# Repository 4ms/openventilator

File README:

This project is a collaboration to update the OpenVentilator files provided by Medtronic to modern KiCad format as well as update BoM to currently available components.

If you'd like to contribute, please contact Seth (seth@kipro-pcb.com) for details.

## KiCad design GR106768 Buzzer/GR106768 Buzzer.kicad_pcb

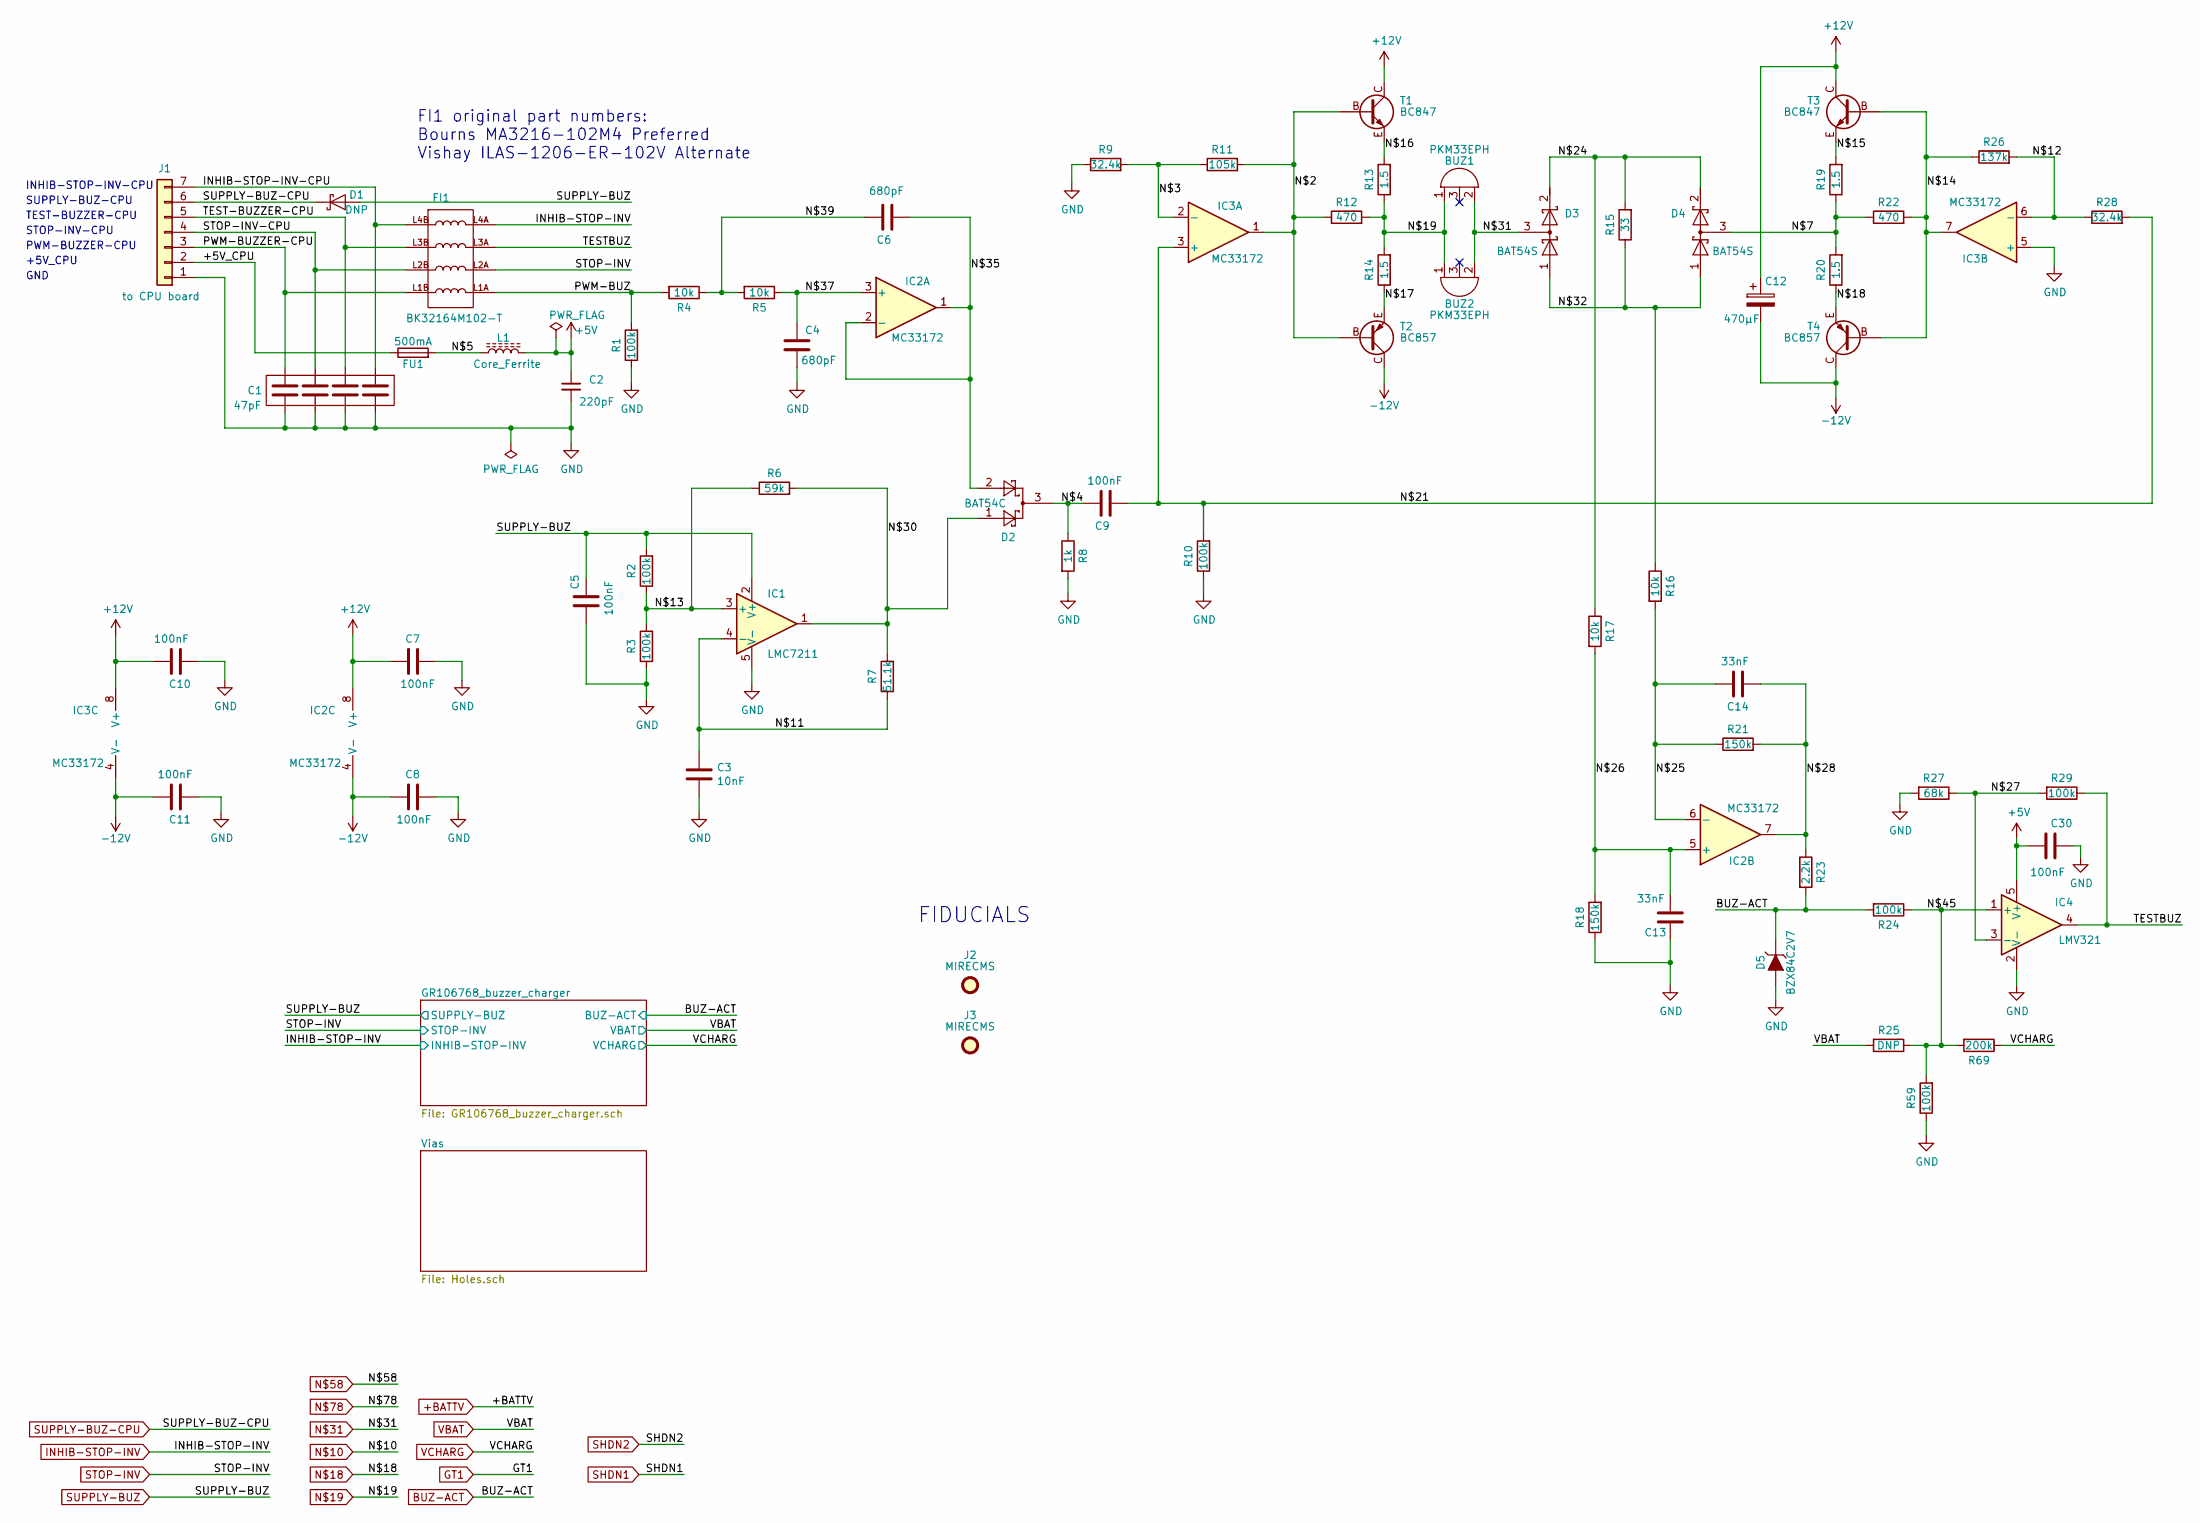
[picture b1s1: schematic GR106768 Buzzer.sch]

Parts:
BUZ1: PKM33EPH; PKM33EPH-1201C_101110111001
BUZ2: PKM33EPH; PKM33EPH-1201C_100110111001
C1: 47pF; C0612-4_1
C2: 220pF; C0402_1b
C3: 10nF; C0805_1b
C4, C6: 680pF; C0402_1b
C5, C7, C8, C9, C10, C11, C30: 100nF; C0402_1b
C12: 470μF; AX10X30_10111011
C13, C14: 33nF; C0603_1b
D1: DNP; DO216AA_1
D2: BAT54C; SOT23-1G_1
D3, D4: BAT54S; SOT23-1G_1
D5: BZX84C2V7; SOT23-1G_1
FI1: BK32164M102-T; WE-FA_1
FU1: 500mA; F6126_1
IC1: LMC7211; SOT23-5_1
IC2, IC3: MC33172; MX.A8_COMPOSANT_1
IC4: LMV321; SOT23-5_1
J1: to CPU board; BAR7-3-2-COVIDIEN_1111100110011001100110011001
J2, J3: MIRECMS; MIRECMS-SAFT_1
L1: Core_Ferrite; RC1206_1
R1, R2, R3, R10, R24, R29, R59: 100k; R0402_1
R4, R5, R16, R17: 10k; R0402_1
R6: 59k; R0402_1
R7: 51.1k; R0402_1
R8: 1k; R0402_1
R9, R28: 32.4k; R0402_1
R11: 105k; R0402_1
R12, R22: 470; R0402_1
R13, R14, R19, R20: 1.5; R0402_1
R15: 33; R0402_1
R18, R21: 150k; R0402_1
R23: 2.2k; R0402_1
R25: DNP; R0402_1
R26: 137k; R0402_1
R27: 68k; R0402_1
R69: 200k; R0402_1
T1, T3: BC847; SOT23-BEC_1
T2, T4: BC857; SOT23-BEC_1

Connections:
+5V: C2.2, C30.1, IC4.5 (V+), L1.2; also elsewhere on the board
+12V: C7.1, C10.2, C12.+, IC2.8 (V+), IC3.8 (V+), T1.C, T3.C; also elsewhere on the board
-12V: C8.1, C11.2, C12.-, IC2.4 (V-), IC3.4 (V-), T2.C, T4.C; also elsewhere on the board
/+5V_CPU: FU1.1, J1.2
/INHIB-STOP-INV-CPU: C1.8, FI1.L4B, J1.7
/N$2: IC3.1, R11.2, R12.1, T1.B, T2.B
/N$3: IC3.2 (-), R9.2, R11.1
/N$4: C9.2, D2.3, R8.1
/N$5: FU1.2, L1.1
/N$7: D4.3, R19.1, R20.2, R22.1
/N$11: C3.2, IC1.4 (-), R7.1
/N$12: IC3.6 (-), R26.2, R28.1
/N$13: IC1.3 (+), R2.1, R3.2, R6.1
/N$14: IC3.7, R22.2, R26.1, T3.B, T4.B
/N$15: R19.2, T3.E
/N$16: R13.2, T1.E
/N$17: R14.1, T2.E
/N$21: C9.1, IC3.3 (+), R10.2, R28.2
/N$24: D3.2, D4.2, R15.2, R17.1
/N$25: C14.1, IC2.6 (-), R16.2, R21.1
/N$26: C13.1, IC2.5 (+), R17.2, R18.2
/N$27: IC4.3 (-), R27.1, R29.2
/N$28: C14.2, IC2.7, R21.2, R23.1
/N$30: D2.1, IC1.1, R6.2, R7.2
/N$32: D3.1, D4.1, R15.1, R16.1
/N$35: C6.1, D2.2, IC2.1, IC2.2 (-)
/N$37: C4.1, IC2.3 (+), R5.1
/N$39: C6.2, R4.1, R5.2
/N$45: IC4.1 (+), R24.1, R25.1, R59.2, R69.2
/PWM-BUZ: FI1.L1A, R1.2, R4.2
/PWM-BUZZER-CPU: C1.5, FI1.L1B, J1.3
/STOP-INV-CPU: C1.6, FI1.L2B, J1.4
/TEST-BUZZER-CPU: C1.7, FI1.L3B, J1.5
/TESTBUZ: FI1.L3A, IC4.4, R29.1
BUZ-ACT: D5.3 (K), R23.2, R24.2; also elsewhere on the board
GND: C1.1, C1.2, C1.3, C1.4, C2.1, C3.1, C4.2, C5.2, C7.2, C8.2, C10.1, C11.1, C13.2, C30.2, D5.1 (A), IC1.5 (V-), IC3.5 (+), IC4.2 (V-), J1.1, R1.1, R3.1, R8.2, R9.1, R10.1, R18.1, R27.2, R59.1; also elsewhere on the board
INHIB-STOP-INV: FI1.L4A; also elsewhere on the board
unnamed 70: R20.1, T4.E; also elsewhere on the board
unnamed 71: BUZ1.1 (G), BUZ2.1 (G), R12.2, R13.1, R14.2; also elsewhere on the board
unnamed 72: BUZ1.2 (M), BUZ2.2 (M), D3.3; also elsewhere on the board
STOP-INV: FI1.L2A; also elsewhere on the board
SUPPLY-BUZ: C5.1, D1.A, IC1.2 (V+), R2.2; also elsewhere on the board
SUPPLY-BUZ-CPU: D1.K, J1.6; also elsewhere on the board
VBAT: R25.2; also elsewhere on the board
VCHARG: R69.1; also elsewhere on the board

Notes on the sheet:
INHIB-STOP-INV-CPU
SUPPLY-BUZ-CPU
TEST-BUZZER-CPU
STOP-INV-CPU
PWM-BUZZER-CPU
+5V_CPU
GND
FIDUCIALS
FI1 original part numbers: Bourns MA3216-102M4 Preferred Vishay ILAS-1206-ER-102V Alternate

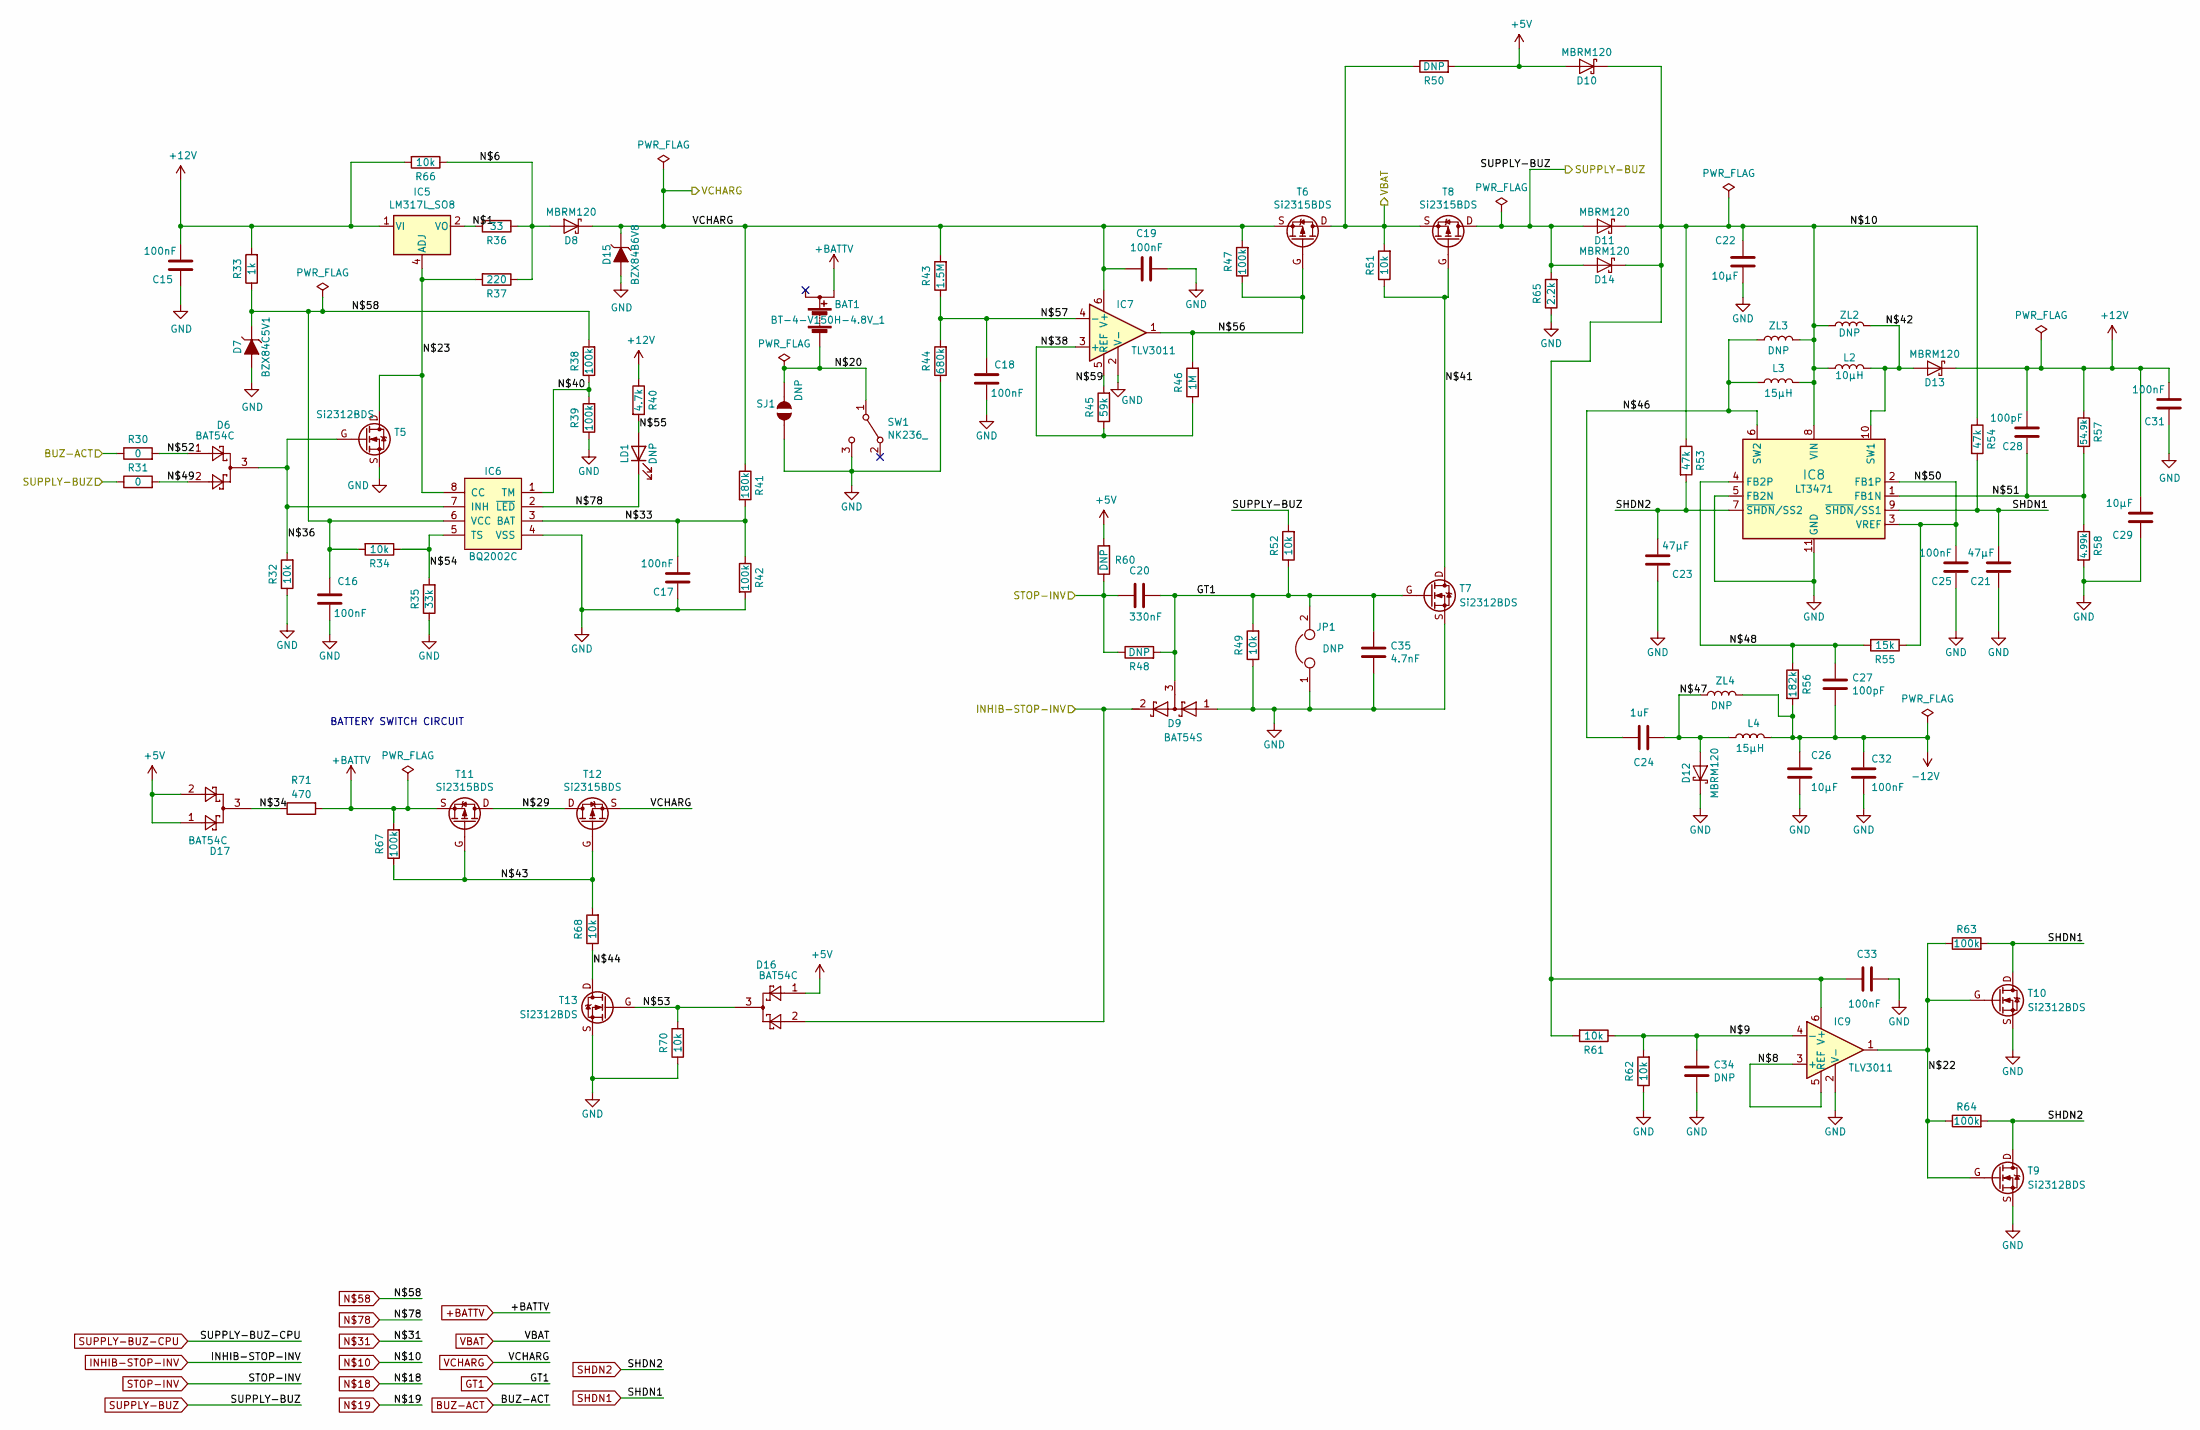
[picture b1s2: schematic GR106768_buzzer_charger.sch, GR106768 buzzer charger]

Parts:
BAT1: BT-4-V150H-4.8V_1; BT-4-V150H-4.8V_100110011001
C15, C16, C17, C18, C19, C25, C31, C32, C33: 100nF; C0402_1b
C20: 330nF; C0603_1b
C21, C23: 47μF; C1210_1
C22, C26, C29: 10μF; RC1206_1
C24: 1uF; C0805_1b
C27, C28: 100pF; C0402_1b
C34: DNP; C0402_1b
C35: 4.7nF; C0402_1b
D6, D16, D17: BAT54C; SOT23-1G_1
D7: BZX84C5V1; SOT23-1G_1
D8, D10, D11, D12, D13, D14: MBRM120; DO216AA_1
D9: BAT54S; SOT23-1G_1
D15: BZX84B6V8; SOT23-1G_1
IC5: LM317L_SO8; MX.A8_COMPOSANT_1
IC6: BQ2002C; MX.A8_COMPOSANT_1
IC7, IC9: TLV3011; SOT23-6_1
IC8: LT3471; DFN10_1
JP1: DNP; TB-CMS-AIROX_1
L2: 10μH; WETPC-S_1
L3, L4: 15μH; WETPC-S_1
LD1: DNP; D0603_1
R30, R31: 0; R0402_1
R32, R34, R49, R51, R52, R61, R62, R66, R68, R70: 10k; R0402_1
R33: 1k; R0402_1
R35: 33k; R0402_1
R36: 33; R0805_1b
R37: 220; R0402_1
R38, R39, R42, R47, R63, R64, R67: 100k; R0402_1
R40: 4.7k; R0402_1
R41: 180k; R0402_1
R43: 1.5M; R0402_1
R44: 680k; R0402_1
R45: 59k; R0402_1
R46: 1M; R0402_1
R48, R50, R60: DNP; R0402_1
R53, R54: 47k; R0402_1
R55: 15k; R0402_1
R56: 182k; R0402_1
R57: 54.9k; R0402_1
R58: 4.99k; R0402_1
R65: 2.2k; R0402_1
R71: 470; R0805_1b
SJ1: DNP; TB-CMS-AIROX-2
SW1: NK236_; NK236_100110011111
T5, T7, T9, T10, T13: Si2312BDS; SOT23-GSD_1
T6, T8, T11, T12: Si2315BDS; SOT23-GSD_1
ZL2: DNP; NR4018_1
ZL3, ZL4: DNP; NR4012_1

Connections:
+5V: D10.A, D16.1, D17.1, D17.2, R50.2, R60.2; also elsewhere on the board
+12V: C15.2, C28.2, C29.2, C31.2, D13.K, IC5.1 (VI), R33.2, R40.1, R57.1, R66.2; also elsewhere on the board
+BATTV: BAT1.+, R67.2, R71.2, T11.S; also elsewhere on the board
-12V: C26.1, C27.1, C32.2, L4.2, R56.2, ZL4.2; also elsewhere on the board
/GR106768_buzzer_charger/N$1: IC5.2 (VO), IC5.3 (VO), IC5.6 (VO), IC5.7 (VO), R36.2
/GR106768_buzzer_charger/N$6: D8.A, R36.1, R37.1, R66.1
/GR106768_buzzer_charger/N$8: IC9.3 (+), IC9.5 (REF)
/GR106768_buzzer_charger/N$9: C34.2, IC9.4 (-), R61.1, R62.2
/GR106768_buzzer_charger/N$20: BAT1.-, SJ1.2, SW1.1 (common)
/GR106768_buzzer_charger/N$22: IC9.1, R63.1, R64.1, T9.G, T10.G
/GR106768_buzzer_charger/N$23: IC5.4 (ADJ), IC6.8 (CC), R37.2, T5.D
/GR106768_buzzer_charger/N$29: T11.D, T12.D
/GR106768_buzzer_charger/N$33: C17.2, IC6.3 (BAT), R41.2, R42.1
/GR106768_buzzer_charger/N$34: D17.3, R71.1
/GR106768_buzzer_charger/N$36: D6.3, IC6.7 (INH), R32.2, T5.G
/GR106768_buzzer_charger/N$38: IC7.3 (+), R45.1, R46.1
/GR106768_buzzer_charger/N$40: IC6.1 (TM), R38.1, R39.2
/GR106768_buzzer_charger/N$41: R51.1, T7.D, T8.G
/GR106768_buzzer_charger/N$42: D13.A, IC8.10 (SW1), L2.2, ZL2.2
/GR106768_buzzer_charger/N$43: R67.1, R68.2, T11.G, T12.G
/GR106768_buzzer_charger/N$44: R68.1, T13.D
/GR106768_buzzer_charger/N$46: C24.2, IC8.6 (SW2), L3.2, ZL3.2
/GR106768_buzzer_charger/N$47: C24.1, D12.A, L4.1, ZL4.1
/GR106768_buzzer_charger/N$48: C27.2, IC8.4 (FB2P), R55.2, R56.1
/GR106768_buzzer_charger/N$49: D6.2, R31.2
/GR106768_buzzer_charger/N$50: C25.2, IC8.2 (FB1P), IC8.3 (VREF), R55.1
/GR106768_buzzer_charger/N$51: C28.1, IC8.1 (FB1N), R57.2, R58.1
/GR106768_buzzer_charger/N$52: D6.1, R30.2
/GR106768_buzzer_charger/N$53: D16.3, R70.2, T13.G
/GR106768_buzzer_charger/N$54: IC6.5 (TS), R34.1, R35.2
/GR106768_buzzer_charger/N$55: LD1.A, R40.2
/GR106768_buzzer_charger/N$56: IC7.1, R46.2, R47.1, T6.G
/GR106768_buzzer_charger/N$57: C18.1, IC7.4 (-), R43.1, R44.2
/GR106768_buzzer_charger/N$59: IC7.5 (REF), R45.2
BUZ-ACT: R30.1; also elsewhere on the board
GND: C15.1, C16.2, C17.1, C18.2, C19.2, C21.1, C22.2, C23.1, C25.1, C26.2, C29.1, C31.1, C32.1, C33.2, C34.1, C35.1, D7.1 (A), D9.1, D12.K, D15.1 (A), IC6.4 (VSS), IC7.2 (V-), IC8.5 (FB2N), IC8.11 (GND), IC9.2 (V-), JP1.1, R32.1, R35.1, R39.1, R42.2, R44.1, R49.1, R58.2, R62.1, R65.1, R70.1, SJ1.1, SW1.3 (cktB), T5.S, T7.S, T9.S, T10.S, T13.S; also elsewhere on the board
GT1: C20.1, C35.2, D9.3, JP1.2, R48.2, R49.2, R52.1, T7.G; also elsewhere on the board
INHIB-STOP-INV: D9.2, D16.2; also elsewhere on the board
unnamed 69: C22.1, C33.1, D10.K, D11.K, D14.K, IC8.8 (VIN), IC9.6 (V+), L2.1, L3.1, R53.1, R54.1, R61.2, ZL2.1, ZL3.1; also elsewhere on the board
unnamed 73: C16.1, D7.3 (K), IC6.6 (VCC), R33.1, R34.2, R38.2; also elsewhere on the board
unnamed 74: IC6.2 (~LED), LD1.K; also elsewhere on the board
SHDN1: C21.2, IC8.9 (~SHDN~/SS1), R54.2, R63.2, T10.D; also elsewhere on the board
SHDN2: C23.2, IC8.7 (~SHDN~/SS2), R53.2, R64.2, T9.D; also elsewhere on the board
STOP-INV: C20.2, R48.1, R60.1; also elsewhere on the board
SUPPLY-BUZ: D11.A, D14.A, R31.1, R52.2, R65.2, T8.D; also elsewhere on the board
VBAT: R50.1, R51.2, T6.D, T8.S; also elsewhere on the board
VCHARG: C19.1, D8.K, D15.3 (K), IC7.6 (V+), R41.1, R43.2, R47.2, T6.S, T12.S; also elsewhere on the board

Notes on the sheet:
BATTERY SWITCH CIRCUIT

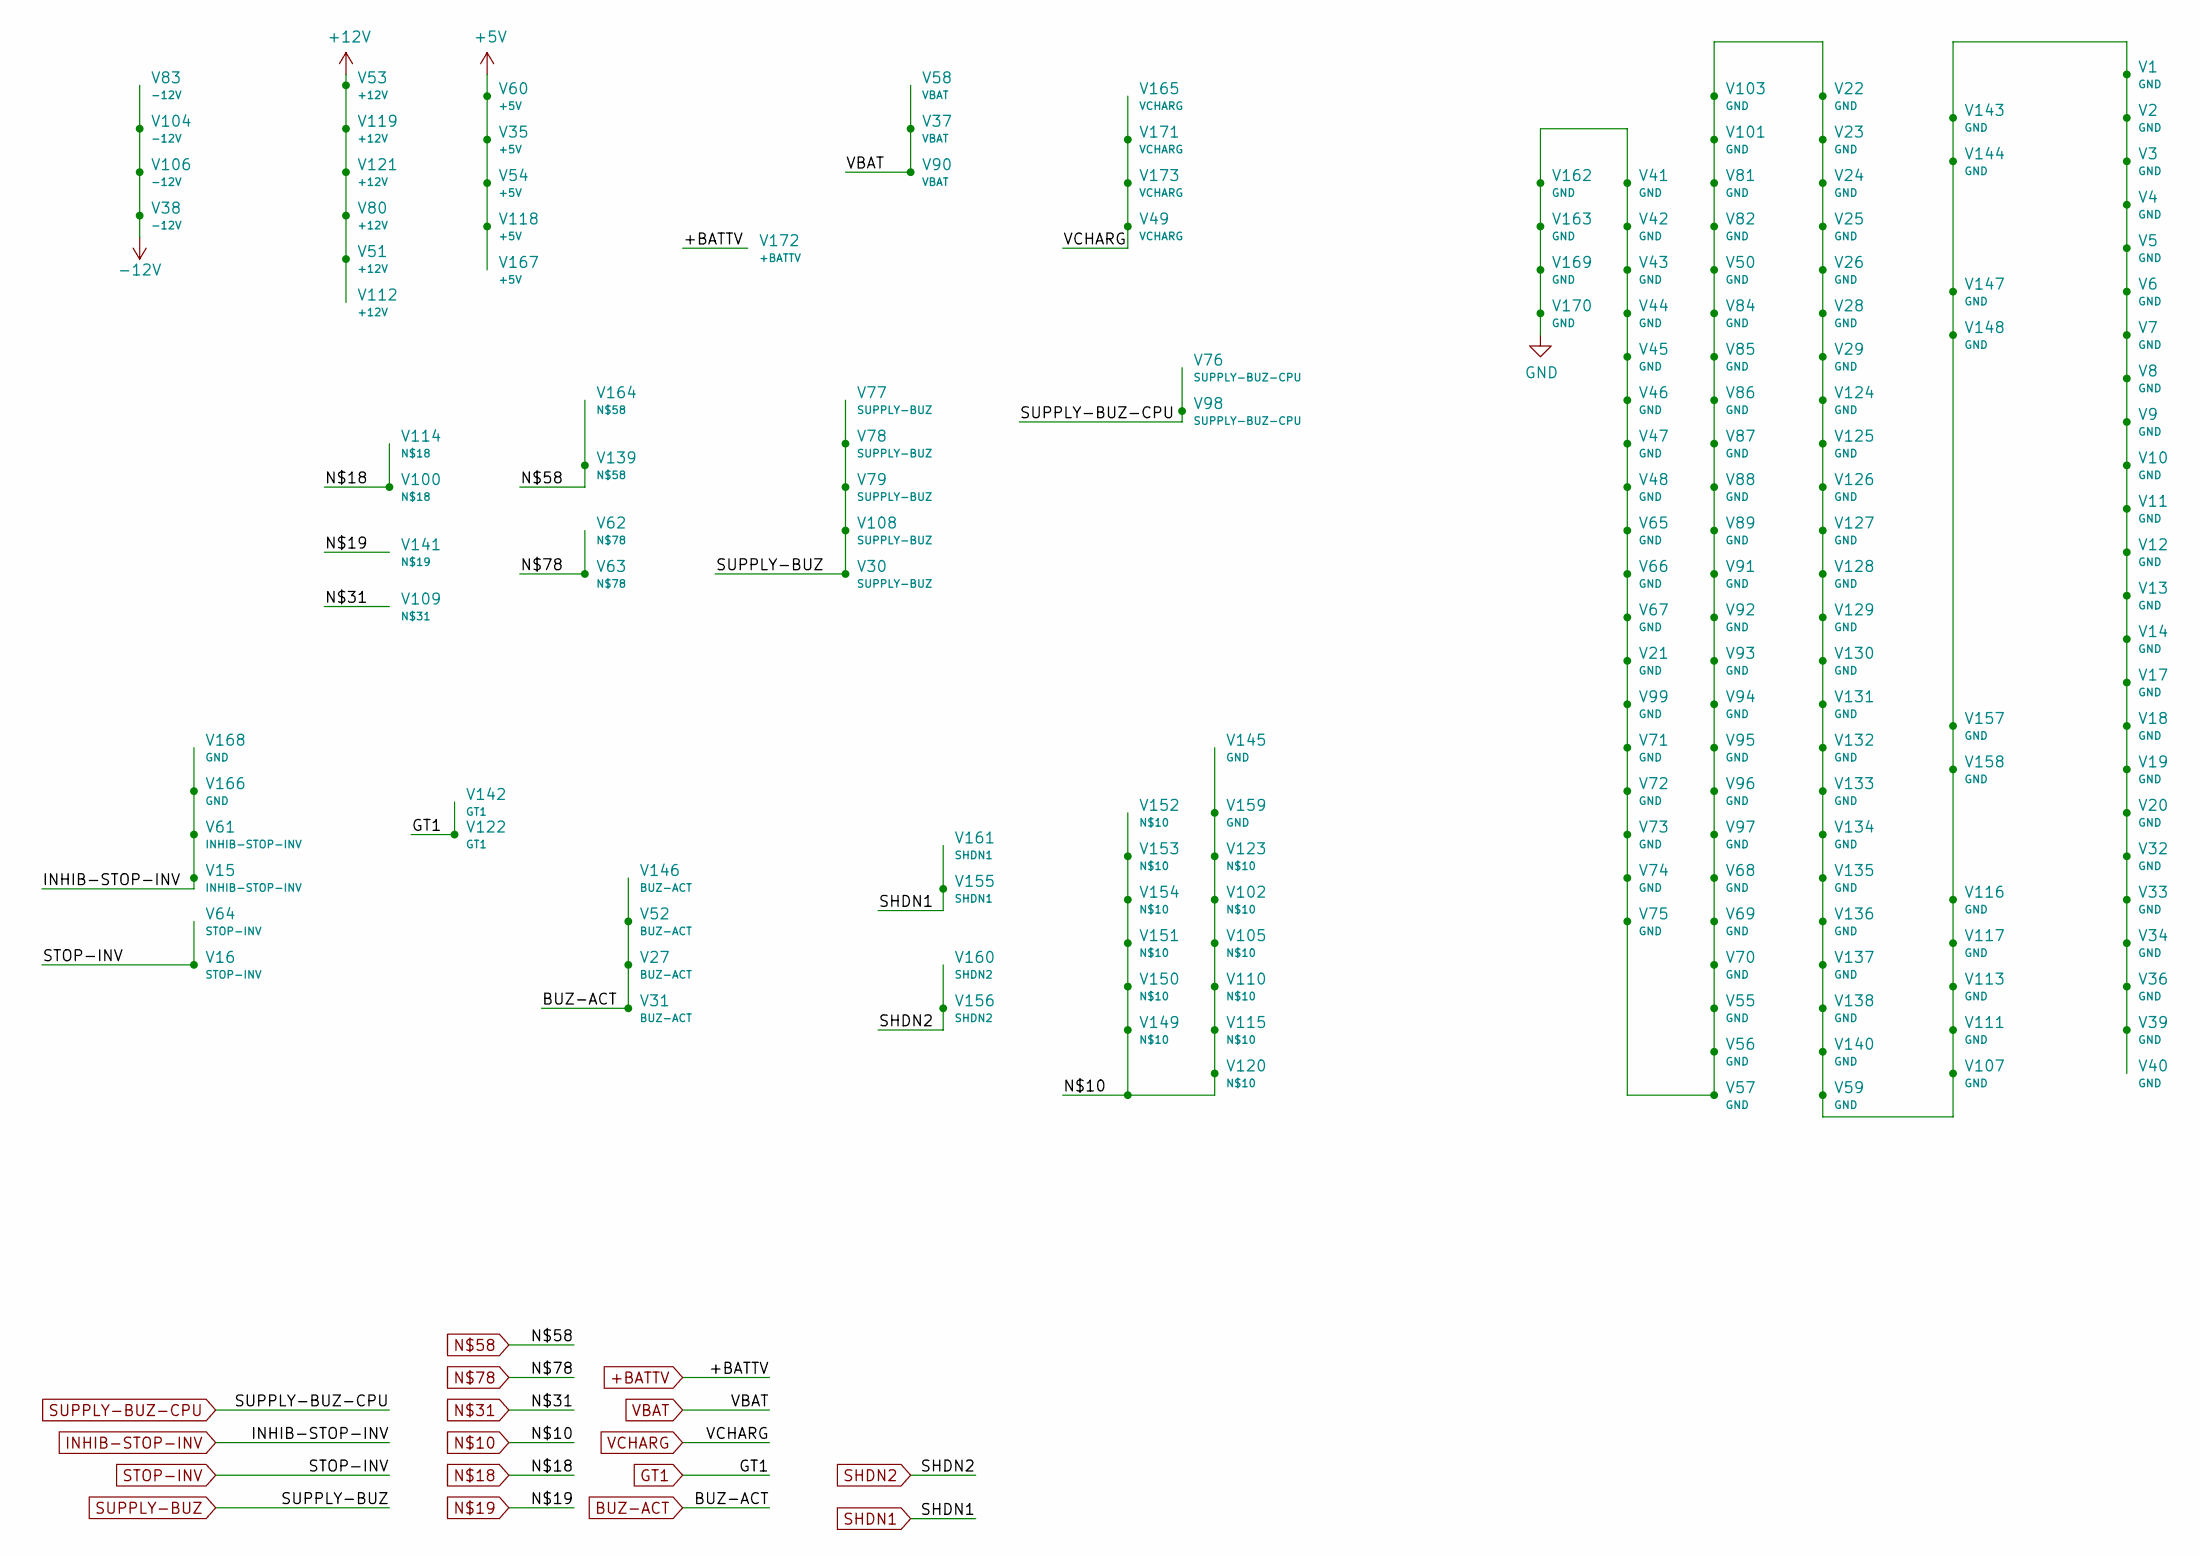
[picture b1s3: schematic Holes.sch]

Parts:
V1, V2, V3, V4, V5, V6, V7, V8, V9, V10, V11, V12, V13, V14, V17, V18, V19, V20, V21, V22, V23, V24, V25, V26, V28, V29, V32, V33, V34, V36, V39, V40, V41, V42, V43, V44, V45, V46, V47, V48, V50, V55, V56, V57, V59, V65, V66, V67, V68, V69, V70, V71, V72, V73, V74, V75, V81, V82, V84, V85, V86, V87, V88, V89, V91, V92, V93, V94, V95, V96, V97, V99, V101, V103, V107, V111, V113, V116, V117, V124, V125, V126, V127, V128, V129, V130, V131, V132, V133, V134, V135, V136, V137, V138, V140, V143, V144, V145, V147, V148, V157, V158, V159, V162, V163, V166, V168, V169, V170: GND; Via_12x32
V15, V61: INHIB-STOP-INV; Via_12x32
V16, V64: STOP-INV; Via_12x32
V27, V31, V52, V146: BUZ-ACT; Via_12x32
V30, V77, V78, V79, V108: SUPPLY-BUZ; Via_12x32
V35, V54, V60, V118, V167: +5V; Via_12x32
V37, V58, V90: VBAT; Via_12x32
V38, V83, V104, V106: -12V; Via_12x32
V49, V165, V171, V173: VCHARG; Via_12x32
V51, V53, V80, V112, V119, V121: +12V; Via_12x32
V62, V63: N$78; Via_12x32
V76, V98: SUPPLY-BUZ-CPU; Via_12x32
V100, V114: N$18; Via_12x32
V102, V105, V110, V115, V120, V123, V149, V150, V151, V152, V153, V154: N$10; Via_12x32
V109: N$31; Via_12x32
V122, V142: GT1; Via_12x32
V139, V164: N$58; Via_12x32
V141: N$19; Via_12x32
V155, V161: SHDN1; Via_12x32
V156, V160: SHDN2; Via_12x32
V172: +BATTV; Via_12x32

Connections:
+5V: V35.~, V54.~, V60.~, V118.~, V167.~; also elsewhere on the board
+12V: V51.~, V53.~, V80.~, V112.~, V119.~, V121.~; also elsewhere on the board
+BATTV: V172.~; also elsewhere on the board
-12V: V38.~, V83.~, V104.~, V106.~; also elsewhere on the board
BUZ-ACT: V27.~, V31.~, V52.~, V146.~; also elsewhere on the board
GND: V1.~, V2.~, V3.~, V4.~, V5.~, V6.~, V7.~, V8.~, V9.~, V10.~, V11.~, V12.~, V13.~, V14.~, V17.~, V18.~, V19.~, V20.~, V21.~, V22.~, V23.~, V24.~, V25.~, V26.~, V28.~, V29.~, V32.~, V33.~, V34.~, V36.~, V39.~, V40.~, V41.~, V42.~, V43.~, V44.~, V45.~, V46.~, V47.~, V48.~, V50.~, V55.~, V56.~, V57.~, V59.~, V65.~, V66.~, V67.~, V68.~, V69.~, V70.~, V71.~, V72.~, V73.~, V74.~, V75.~, V81.~, V82.~, V84.~, V85.~, V86.~, V87.~, V88.~, V89.~, V91.~, V92.~, V93.~, V94.~, V95.~, V96.~, V97.~, V99.~, V101.~, V103.~, V107.~, V111.~, V113.~, V116.~, V117.~, V124.~, V125.~, V126.~, V127.~, V128.~, V129.~, V130.~, V131.~, V132.~, V133.~, V134.~, V135.~, V136.~, V137.~, V138.~, V140.~, V143.~, V144.~, V147.~, V148.~, V157.~, V158.~, V162.~, V163.~, V169.~, V170.~; also elsewhere on the board
GT1: V122.~, V142.~; also elsewhere on the board
INHIB-STOP-INV: V15.~, V61.~, V166.~, V168.~; also elsewhere on the board
unnamed 69: V102.~, V105.~, V110.~, V115.~, V120.~, V123.~, V145.~, V149.~, V150.~, V151.~, V152.~, V153.~, V154.~, V159.~; also elsewhere on the board
unnamed 70: V100.~, V114.~; also elsewhere on the board
unnamed 71: V141.~; also elsewhere on the board
unnamed 72: V109.~; also elsewhere on the board
unnamed 73: V139.~, V164.~; also elsewhere on the board
unnamed 74: V62.~, V63.~; also elsewhere on the board
SHDN1: V155.~, V161.~; also elsewhere on the board
SHDN2: V156.~, V160.~; also elsewhere on the board
STOP-INV: V16.~, V64.~; also elsewhere on the board
SUPPLY-BUZ: V30.~, V77.~, V78.~, V79.~, V108.~; also elsewhere on the board
SUPPLY-BUZ-CPU: V76.~, V98.~; also elsewhere on the board
VBAT: V37.~, V58.~, V90.~; also elsewhere on the board
VCHARG: V49.~, V165.~, V171.~, V173.~; also elsewhere on the board

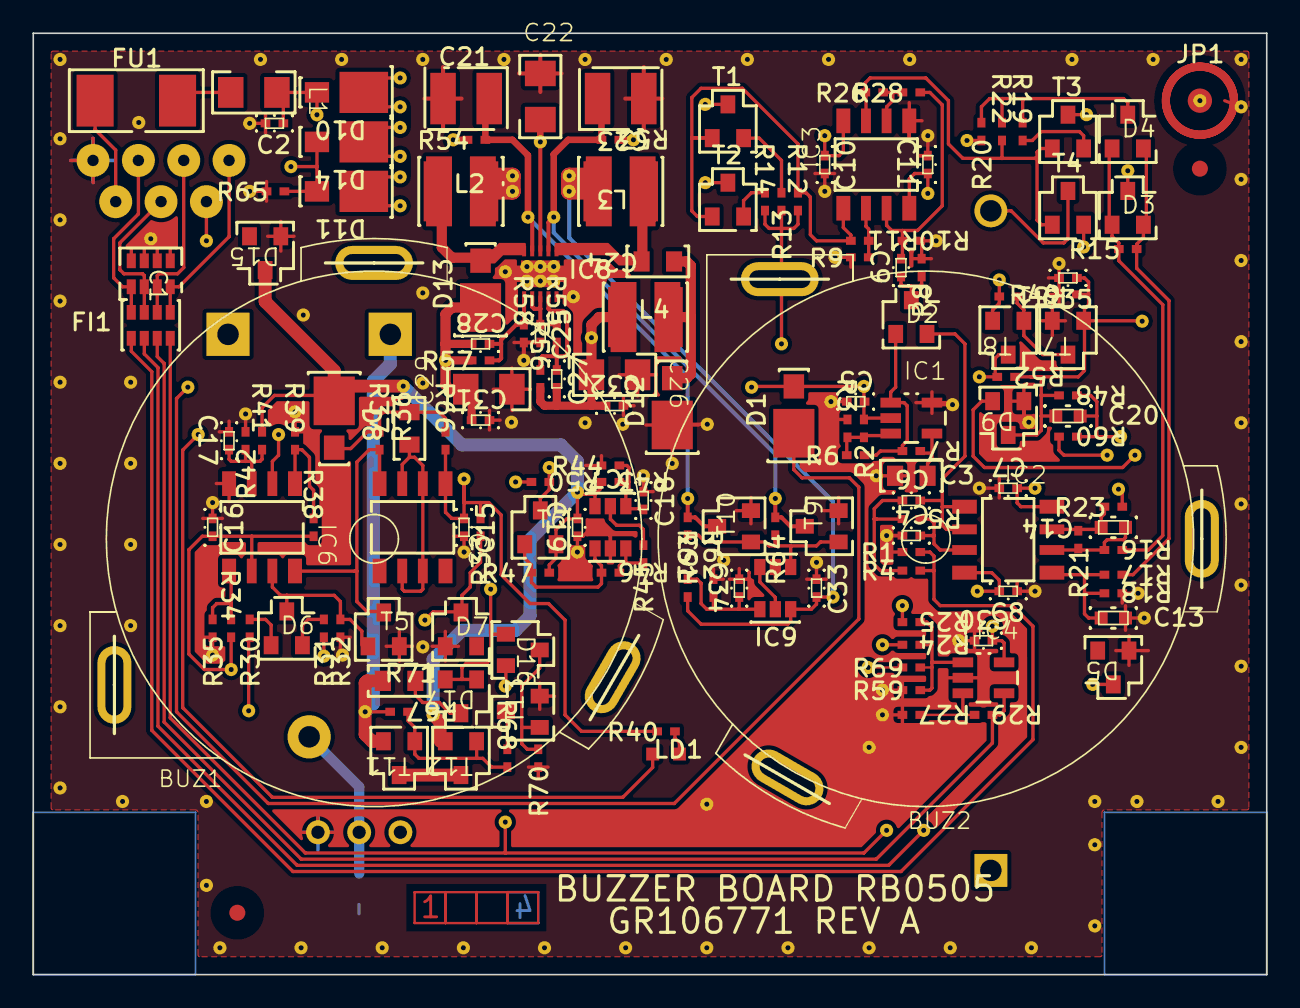
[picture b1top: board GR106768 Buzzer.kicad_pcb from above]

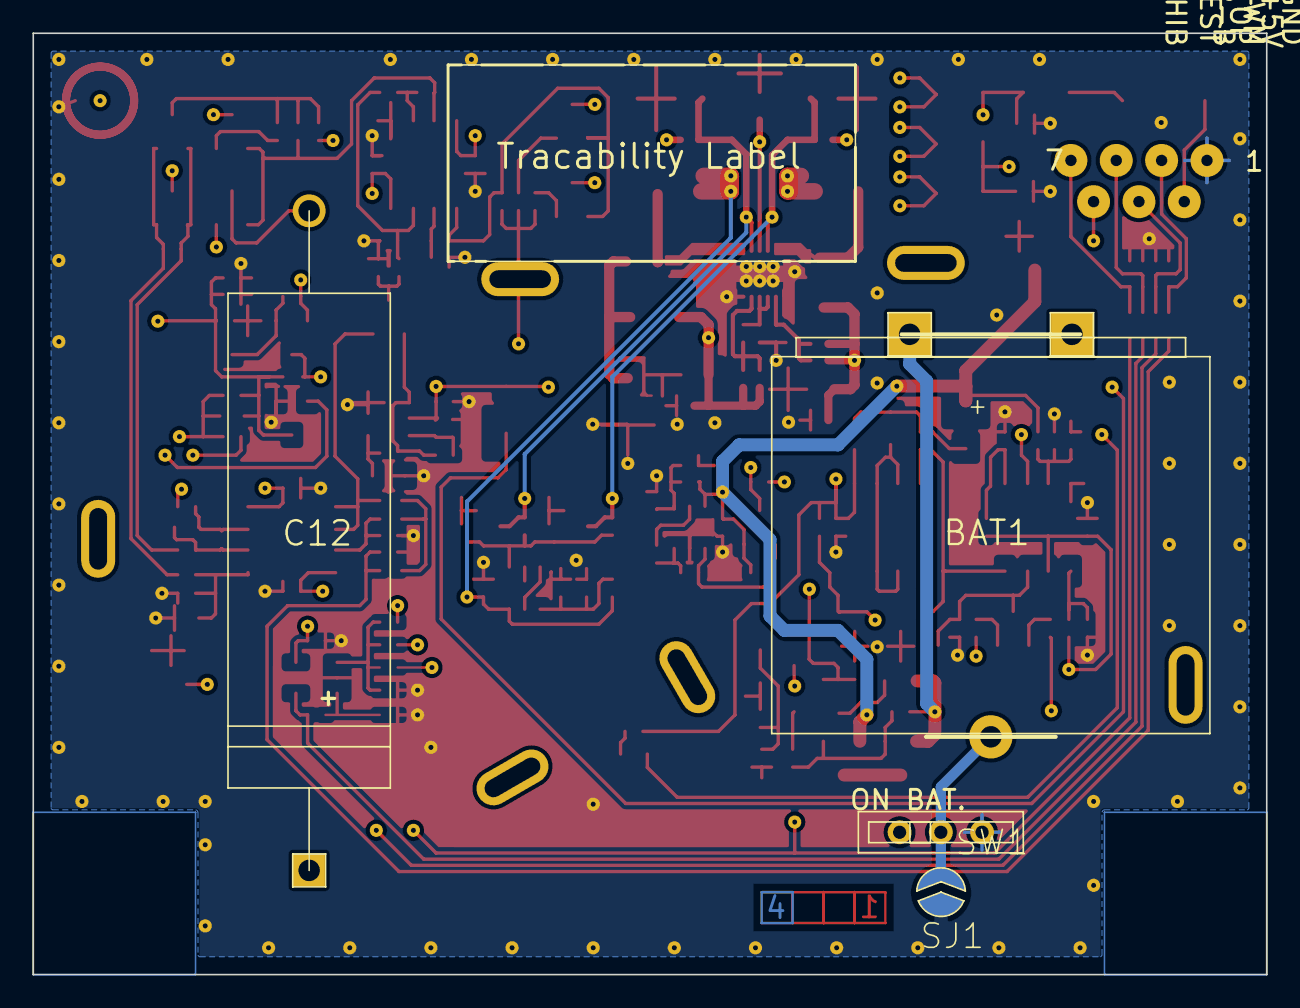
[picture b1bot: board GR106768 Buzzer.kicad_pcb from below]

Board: 4 copper layers, 76.0 x 58.0 mm, 342 parts (4 on the bottom side), 82 nets.

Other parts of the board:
cam2: PER-COVIDIEN_TEXTE
cam6, cam7, cam8, cam9: COIN_EXTERNE; COIN_EXTERNE_1

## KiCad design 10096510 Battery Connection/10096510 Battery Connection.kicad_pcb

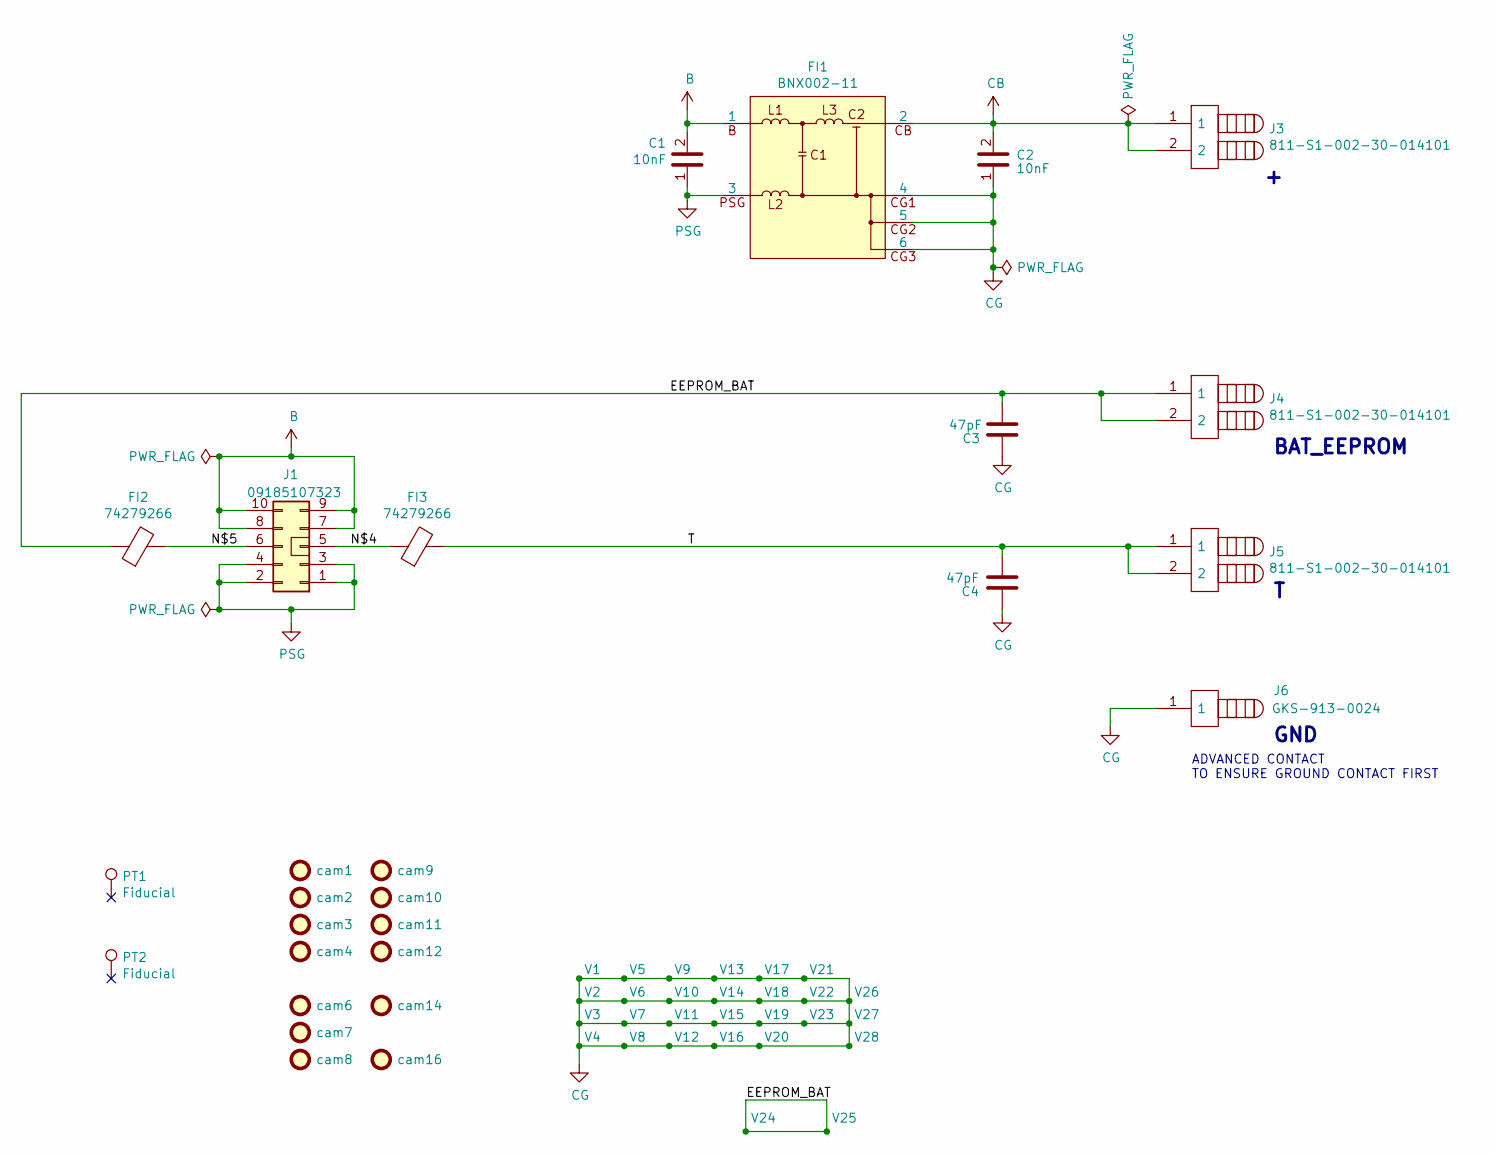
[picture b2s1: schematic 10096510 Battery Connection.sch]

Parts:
C1, C2: 10nF; C0603
C3, C4: 47pF; C0402
FI1: BNX002-11; BNX002
FI2, FI3: 74279266; C0603
J1: 09185107323; BP2X5C
J3, J4, J5: 811-S1-002-30-014101; 811S1-02
J6: GKS-913-0024; GKS913
PT1, PT2: Fiducial; MIRECMS_D-1.5
V1, V2, V3, V4, V5, V6, V7, V8, V9, V10, V11, V12, V13, V14, V15, V16, V17, V18, V19, V20, V21, V22, V23, V24, V25, V26, V27, V28: Via; VIA-100X04-VE
cam1: FILM18_HORIZONTAL
cam2: A3_EQFC_COVIDIEN
cam3: PER-COVIDIEN_TEXTE
cam4: A3_EQFS_COVIDIEN
cam6, cam7, cam8, cam9: COIN_EXTERNE_0.5
cam10: A3_PER_COVIDIEN
cam11, cam16: FEE_COMP_0.3
cam12: FABRICATION-FEE
cam14: PERCAGE-MC_TABLEAU

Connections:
/EEPROM_BAT: C3.2, FI2.1, J4.1, J4.2, V24.~, V25.~
/N$4: FI3.1, J1.5
/N$5: FI2.2, J1.6
/T: C4.2, FI3.2, J5.1, J5.2
B: C1.2, FI1.B (1), J1.7, J1.8, J1.9, J1.10
CB: C2.2, FI1.CB (2), J3.1, J3.2
CG: C2.1, C3.1, C4.1, FI1.CG1 (4), FI1.CG2 (5), FI1.CG3 (6), J6.1, V1.~, V2.~, V3.~, V4.~, V5.~, V6.~, V7.~, V8.~, V9.~, V10.~, V11.~, V12.~, V13.~, V14.~, V15.~, V16.~, V17.~, V18.~, V19.~, V20.~, V21.~, V22.~, V23.~, V26.~, V27.~, V28.~
PSG: C1.1, FI1.PSG (3), J1.1, J1.2, J1.3, J1.4

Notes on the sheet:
ADVANCED CONTACT TO ENSURE GROUND CONTACT FIRST
BAT_EEPROM
GND

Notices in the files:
parts and their libraries:
Copyright C 2012, Covidien
